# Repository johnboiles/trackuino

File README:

Trackuino
=========
Firmware to turn your Arduino into an APRS tracker. This is a fork of the [original mercurial repo](http://code.google.com/p/trackuino) by EA5HAV Javi.

Board support
-------------
Arduinos based on ATmega328 (e.g. Uno), ATmega32u4 (e.g. Arduino Leonardo), and chipKIT Uno32 are supported. Here are a couple PCB designs that work with this firmware:

* [Official Trackuino Shield](https://code.google.com/p/trackuino/wiki/TrackuinoShield22)
* [TinyTrackuino](https://github.com/johnboiles/tinytrackuino)

Building with the Arduino IDE
-----------------------------

1. Open `trackuino/trackuino.ino`
2. Locate the `config.h` tab and replace settings with your own (`S_CALLSIGN`, `APRS_COMMENT`, etc).
3. Select the appropriate board for your hardware setup
4. Click Upload

On ATmega328 and other boards with only a single serial port, make sure to unplug the GPS when uploading or flashing will fail with an error.

Building at the command line
----------------------------
A makefile is included for easy building and uploading outside the Arduino IDE. The `BOARD` environment variable needs to be specified so the makefile can know what board to compile for. For boards not included in the official Arduino IDE, you can set `BOARDSPATH` to point at a directory that has details about the board.

For example, for an Arduino UNO (included in the Arduino IDE)

    BOARD=uno make upload

Or for a Sparkfun ProMicro 5V/16MHz board (assuming Sparkfun boards are installed in `~/Documents/Arduino/hardware`)

    BOARD=promicro16 BOARDSPATH=~/Documents/Arduino/hardware/sf32u4_boards make upload

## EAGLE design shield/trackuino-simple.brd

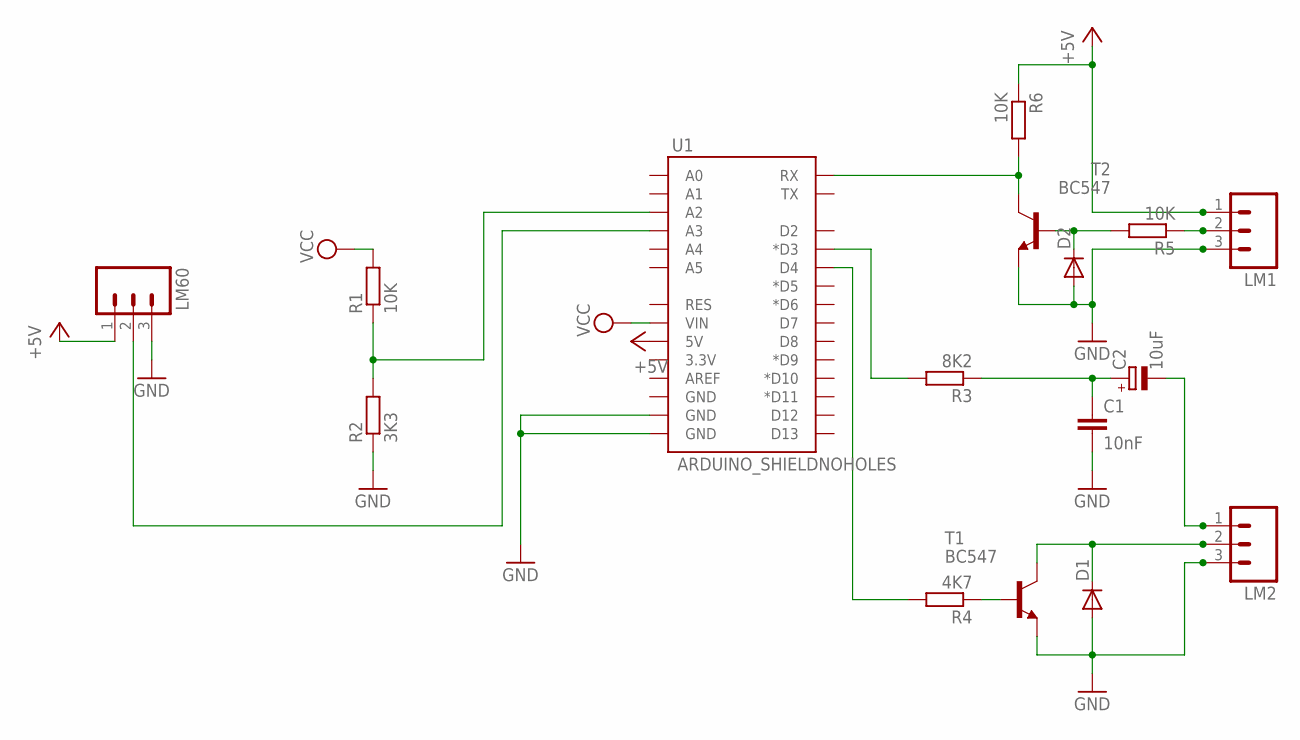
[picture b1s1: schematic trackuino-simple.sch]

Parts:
C1: 10nF; C050-025X075
C2: 10uF; E2,5-6
D1, D2: DIODE-DO41-10; DO41-10
LM1, LM2, LM60: M03PTH; 1X03
R1, R5, R6: 10K; 0207/10
R2: 3K3; 0207/10
R3: 8K2; 0207/10
R4: 4K7; 0207/10
T1, T2: BC547; TO92
U1: ARDUINO_SHIELDNOHOLES; DUEMILANOVE_SHIELD_NOHOLES

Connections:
+5V: LM1.1, LM60.1, R6.1, U1.5V
A0: R1.1, R2.2, U1.A2
GND: C1.2, D1.A, D2.A, LM1.3, LM2.3, LM60.3, R2.1, T1.1 (E), T2.1 (E), U1.GND@0 (GND), U1.GND@1 (GND)
unnamed: R6.2, T2.3 (C), U1.RX
unnamed: LM60.2, U1.A3
unnamed: R4.2, U1.D4
unnamed: R4.1, T1.2 (B)
unnamed: D2.C, R5.2, T2.2 (B)
unnamed: R3.2, U1.D3 (*D3)
unnamed: D1.C, LM2.2, T1.3 (C)
unnamed: C1.1, C2.+, R3.1
unnamed: C2.-, LM2.1
unnamed: LM1.2, R5.1
VCC: R1.2, U1.VIN

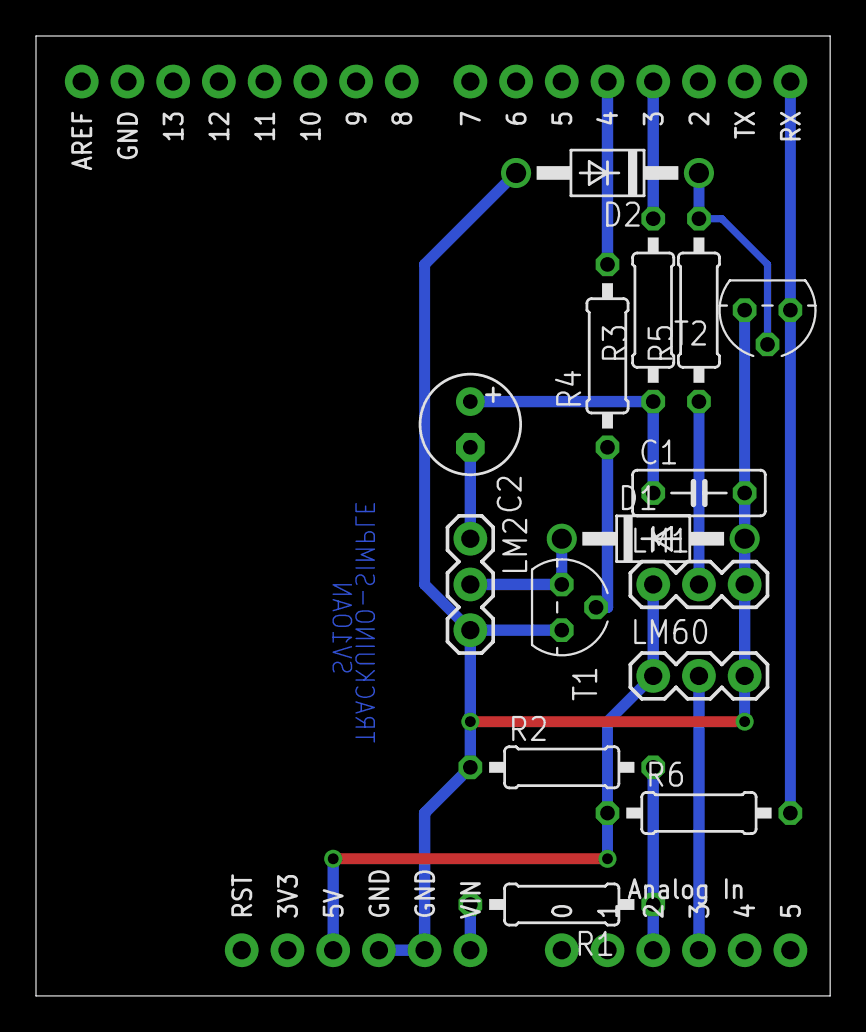
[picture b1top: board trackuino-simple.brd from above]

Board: 2 copper layers, 44.1 x 53.3 mm, 16 parts (0 on the bottom side), 14 nets.

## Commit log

2012-07-15 Fixed modem playback too off of the nominal baud rate (1200) due to integer approximations
2012-08-26 - Added pic32 (Chipkit Uno32) compatibility - Slotted transmissions for multilaunch events - Active/passive buzzer support (DC/PWM driven) - Removed MX146 support - Battery (Vin) voltage sensing - Br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
2012-08-26 Added readme, license and whatsnew files
2013-05-06 Import Trackuino source
2013-05-06 Convert to Arduino 1.0
2013-05-06 Option to operate without GPS
2013-05-06 Option to use an LCD
2013-05-06 Option to disable external temperature sensor
2013-05-18 Add shield schematic and PCB
2013-05-26 Serial GPS support for shield
2013-05-26 Change output filter capacitor value
2013-08-09 Adding command-line makefile
2013-09-06 Support for disabling the internal LM60
2013-09-06 Hopefully working support atmega32u4 based arduinos (untested). Does not work with the buzzer in passive mode
2013-09-07 Support for using timer 4 on atmega32u4 processors
2013-09-25 Fixing internal reference voltage for 32u4 based avrs
2013-09-25 Using a #define to specify a different serial port for GPS on Atmega32u4
2013-10-13 Breaking out configs into per-board files
2013-10-13 Removing half-baked shield files
2014-04-06 - fix WProgram.h -> Arduino.h headers enables compilation on arduino 1.0+ - added flag for 2200 Hz tone pre-emphasis (actually done by de-emphasizing the 1200 Hz tone). Makes picky TNCs happier and a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
2014-04-06 update whatsnew
2014-07-25 - renamed .pde to .ino since arduino <1.0 is old enough - gcc 4.3.2 (Arduino 1.0.x) -> 4.8.1 (Arduino 1.5.x) deprecates prog_uchar, PROGMEM is now required
2014-09-13 Support for disabling the internal LM60
    Conflicts:
    .gitignore
2014-09-13 Hopefully working support atmega32u4 based arduinos (untested). Does not work with the buzzer in passive mode
    Conflicts:
    trackuino/modem_avr.cpp
2014-09-13 Support for using timer 4 on atmega32u4 processors
    Conflicts:
    trackuino/modem_avr32u4.cpp
2014-09-13 Breaking out configs into per-board files
    Conflicts:
    trackuino/config.h
    trackuino/modem_avr32u4.cpp
2014-09-13 Makefile for building at the commandline
2014-09-13 Updating README
2014-09-13 Renaming README to README.md
2016-11-19 Update link to original trackuino
2017-09-20 Replace deprecated prog_uchar with PROGMEM
